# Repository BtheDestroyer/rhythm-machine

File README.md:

# rhythm-machine

Arcade style rhythm game powered by the RP2040 microprocessor.

## To Do

- The Pico's power supply isn't sufficient for running the amp + speaker. A new one will have to be added to the PCB.
- The audio amp and SD card reader modules should be worked into the PCB directly rather than third-party items.
- Potentially ditch the Pico by integrating the RP2040 into the main PCB directly.

## Materials

Most links below are to Adafruit. None are affiliate links.

- 1x [Raspberry Pi Pico](https://www.adafruit.com/product/4864)
- 1x [3 inch, 3 watt speaker](https://www.adafruit.com/product/1314)
- 6x [Arcade buttons](https://www.adafruit.com/product/473)
  - Note: Get 2 of 3 different colors; Red + Green + Bluefloat
- 6x [Quick-connect JST cables](https://www.adafruit.com/product/1152)
  - Note: The link is to a pack of 10, so just one pack will be sufficient.
- 6x [2-Pin JST-XH connectors](https://www.digikey.com/en/products/detail/jst-sales-america-inc/B2B-XH-A-LF-SN/1651045)
- 1x [Micro SD card slot breakout board](https://www.adafruit.com/product/4682)
  - [Bulk alternative](https://www.amazon.com/gp/product/B0989SM146/)
- 1x [Micro SD card](https://www.amazon.com/SanDisk-COMINU024966-16GB-microSD-Card/dp/B004KSMXVM/)
  - Note: Avoid overpaying for these for projects. I'd recommend getting [a pack of 10 cards](https://www.amazon.com/dp/B0876H387X) between 8 and 32 GB.
- 1x [Class D audio amp](https://www.adafruit.com/product/2130)
- 1x [1602 LCD with 3.3v I2C adapter](https://www.amazon.com/gp/product/B08MPTND1V/)
  - Note: You can buy these pre-soldered, but you'll need to trim the pins down which may damage your wire cutters. I'd recommend getting some [cheap disposable ones](https://www.amazon.com/Hakko-CHP-170-Micro-Cutter/dp/B00FZPDG1K/) for this purpose.
- 45x [WS2812 addressable RGB LEDs](https://www.amazon.com/gp/product/B088BRY2SH/)
  - Note: Only 44 will be visible, but I'm using one as a makeshift logic level shifter.
- 1x Zener diode
  - [Various diode pack](https://www.amazon.com/EEEEE-Assortment-Rectifier-Recovery-Switching/dp/B08SBTS2KZ/)
  - This is only necessary if you're using one of the LEDs as a makeshift logic level shifter. If you have a dedicated logic level shifter, this isn't necessary
- 1x [75mm 10 kOhm Linear Slide Potentiometer](https://www.amazon.com/dp/B09NX39NWR?psc=1&ref=ppx_yo2ov_dt_b_product_details)
- 1x 47uF capacitor
  - [Electrolytic capacitor pack](https://www.amazon.com/BOJACK-Electrolytic-Capacitor-Assortment-0-1uF－1000uF/dp/B07PBQXQNQ/)
- 1x 10nF capacitor
  - [Ceramic capacitor pack](https://www.amazon.com/DYWISHKEY-Monolithic-Multilayer-Capacitors-0-1uF-100nF/dp/B07QGDGGZV/)
- 1x 100 Ohm resistor
- 1x 220 Ohm resistor
- 1x 1.8 kOhm resistor
  - [Resistor pack](https://www.amazon.com/BOJACK-Values-Resistor-Resistors-Assortment/dp/B08FD1XVL6/)
- 4x M3 6mm screws
- 4x M3 8mm screws
- 8x M3 nuts
- 2x M3 heat-set inserts
- 2x M2 8mm screws
  - For the above assembly hardware, I'd highly recommend just searching around for a kit. There are many options that offer different screw sizes, heads, bits, etc.

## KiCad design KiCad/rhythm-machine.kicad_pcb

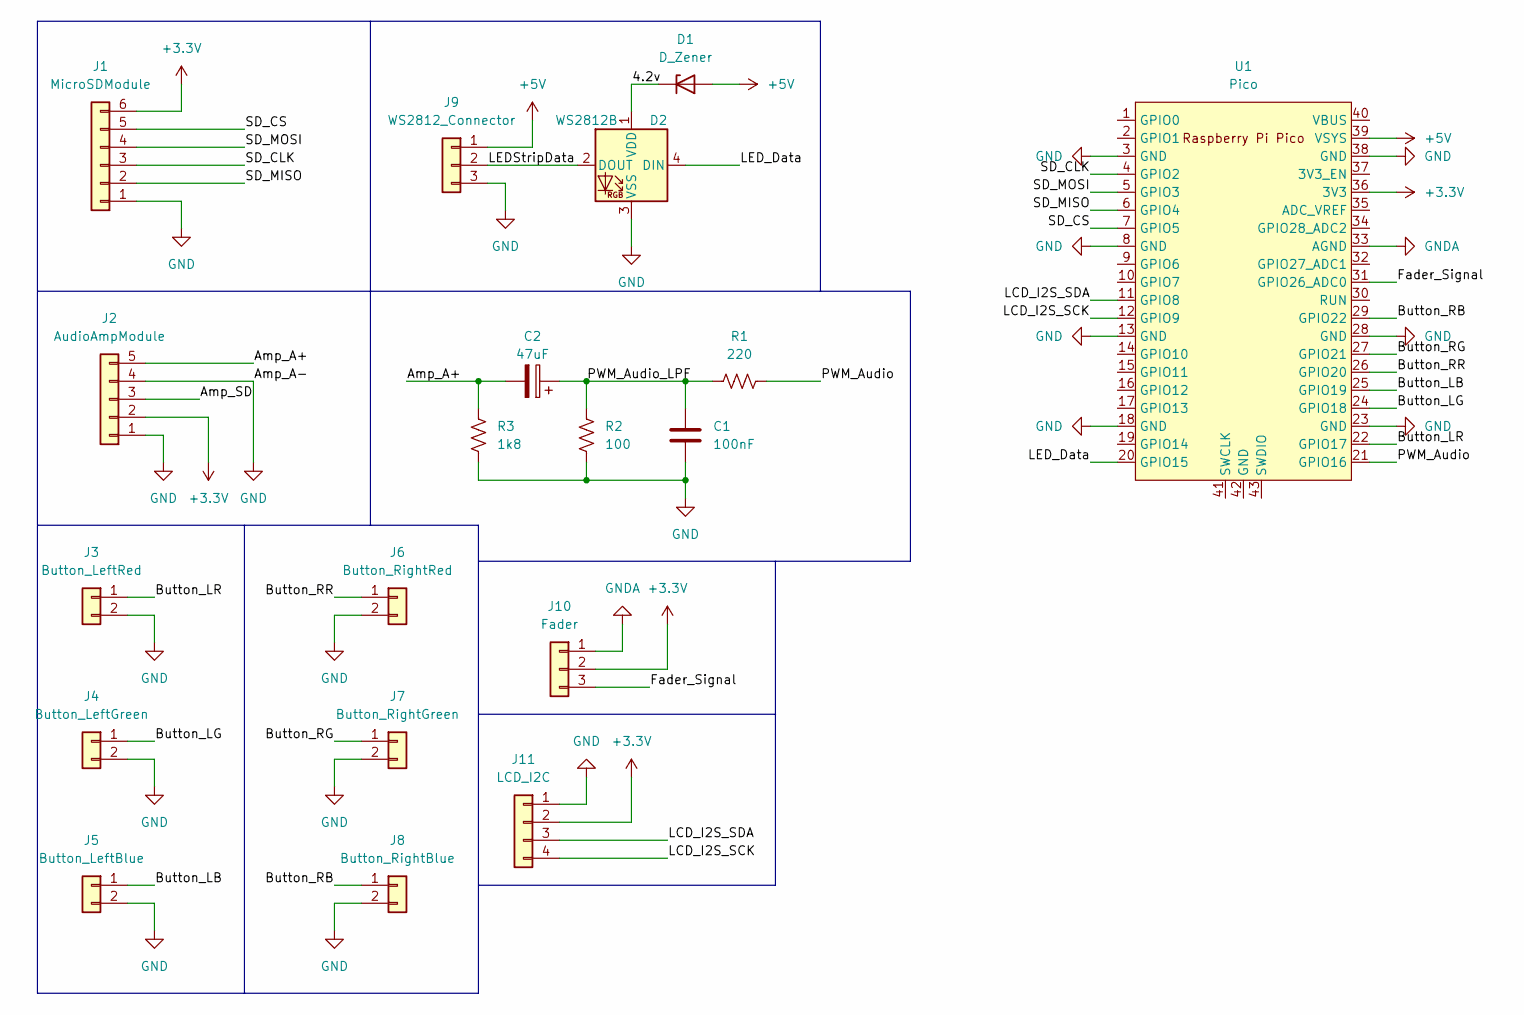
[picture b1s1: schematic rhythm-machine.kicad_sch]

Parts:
C1: 100nF; C_Disc_D4.3mm_W1.9mm_P5.00mm
C2: 47uF; CP_Radial_D4.0mm_P2.00mm
D1: D_Zener; D_T-1_P5.08mm_Horizontal
D2: WS2812B; WS2812B_Strip_Single
J1: MicroSDModule; PinHeader_1x06_P2.54mm_Vertical
J2: AudioAmpModule; PinHeader_1x05_P2.54mm_Vertical
J3: Button_LeftRed; JST_XH_B2B-XH-A_1x02_P2.50mm_Vertical
J4: Button_LeftGreen; JST_XH_B2B-XH-A_1x02_P2.50mm_Vertical
J5: Button_LeftBlue; JST_XH_B2B-XH-A_1x02_P2.50mm_Vertical
J6: Button_RightRed; JST_XH_B2B-XH-A_1x02_P2.50mm_Vertical
J7: Button_RightGreen; JST_XH_B2B-XH-A_1x02_P2.50mm_Vertical
J8: Button_RightBlue; JST_XH_B2B-XH-A_1x02_P2.50mm_Vertical
J9: WS2812_Connector; PinHeader_1x03_P2.54mm_Vertical
J10: Fader; PinHeader_1x03_P2.54mm_Vertical
J11: LCD_I2C; PinHeader_1x04_P2.54mm_Vertical
R1: 220; R_Axial_DIN0207_L6.3mm_D2.5mm_P7.62mm_Horizontal
R2: 100; R_Axial_DIN0207_L6.3mm_D2.5mm_P7.62mm_Horizontal
R3: 1k8; R_Axial_DIN0207_L6.3mm_D2.5mm_P7.62mm_Horizontal
U1: Pico; RPi_Pico_SMD_TH

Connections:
+3V3: J1.6, J2.2, J10.2, J11.2, U1.36 (3V3)
+5V: D1.2 (A), J9.1, U1.39 (VSYS)
/4.2v: D1.1 (K), D2.1 (VDD)
/Amp_A+: C2.2, J2.5, R3.2
/Amp_SD: J2.3
/Button_LB: J5.1, U1.25 (GPIO19)
/Button_LG: J4.1, U1.24 (GPIO18)
/Button_LR: J3.1, U1.22 (GPIO17)
/Button_RB: J8.1, U1.29 (GPIO22)
/Button_RG: J7.1, U1.27 (GPIO21)
/Button_RR: J6.1, U1.26 (GPIO20)
/Fader_Signal: J10.3, U1.31 (GPIO26_ADC0)
/LCD_I2S_SCK: J11.4, U1.12 (GPIO9)
/LCD_I2S_SDA: J11.3, U1.11 (GPIO8)
/LEDStripData: D2.2 (DOUT), J9.2
/LED_Data: D2.4 (DIN), U1.20 (GPIO15)
/PWM_Audio: R1.2, U1.21 (GPIO16)
/PWM_Audio_LPF: C1.2, C2.1, R1.1, R2.2
/SD_CLK: J1.3, U1.4 (GPIO2)
/SD_CS: J1.5, U1.7 (GPIO5)
/SD_MISO: J1.2, U1.6 (GPIO4)
/SD_MOSI: J1.4, U1.5 (GPIO3)
GND: C1.1, D2.3 (VSS), J1.1, J2.1, J2.4, J3.2, J4.2, J5.2, J6.2, J7.2, J8.2, J9.3, J11.1, R2.1, R3.1, U1.3 (GND), U1.8 (GND), U1.13 (GND), U1.18 (GND), U1.23 (GND), U1.28 (GND), U1.38 (GND)
GNDA: J10.1, U1.33 (AGND)

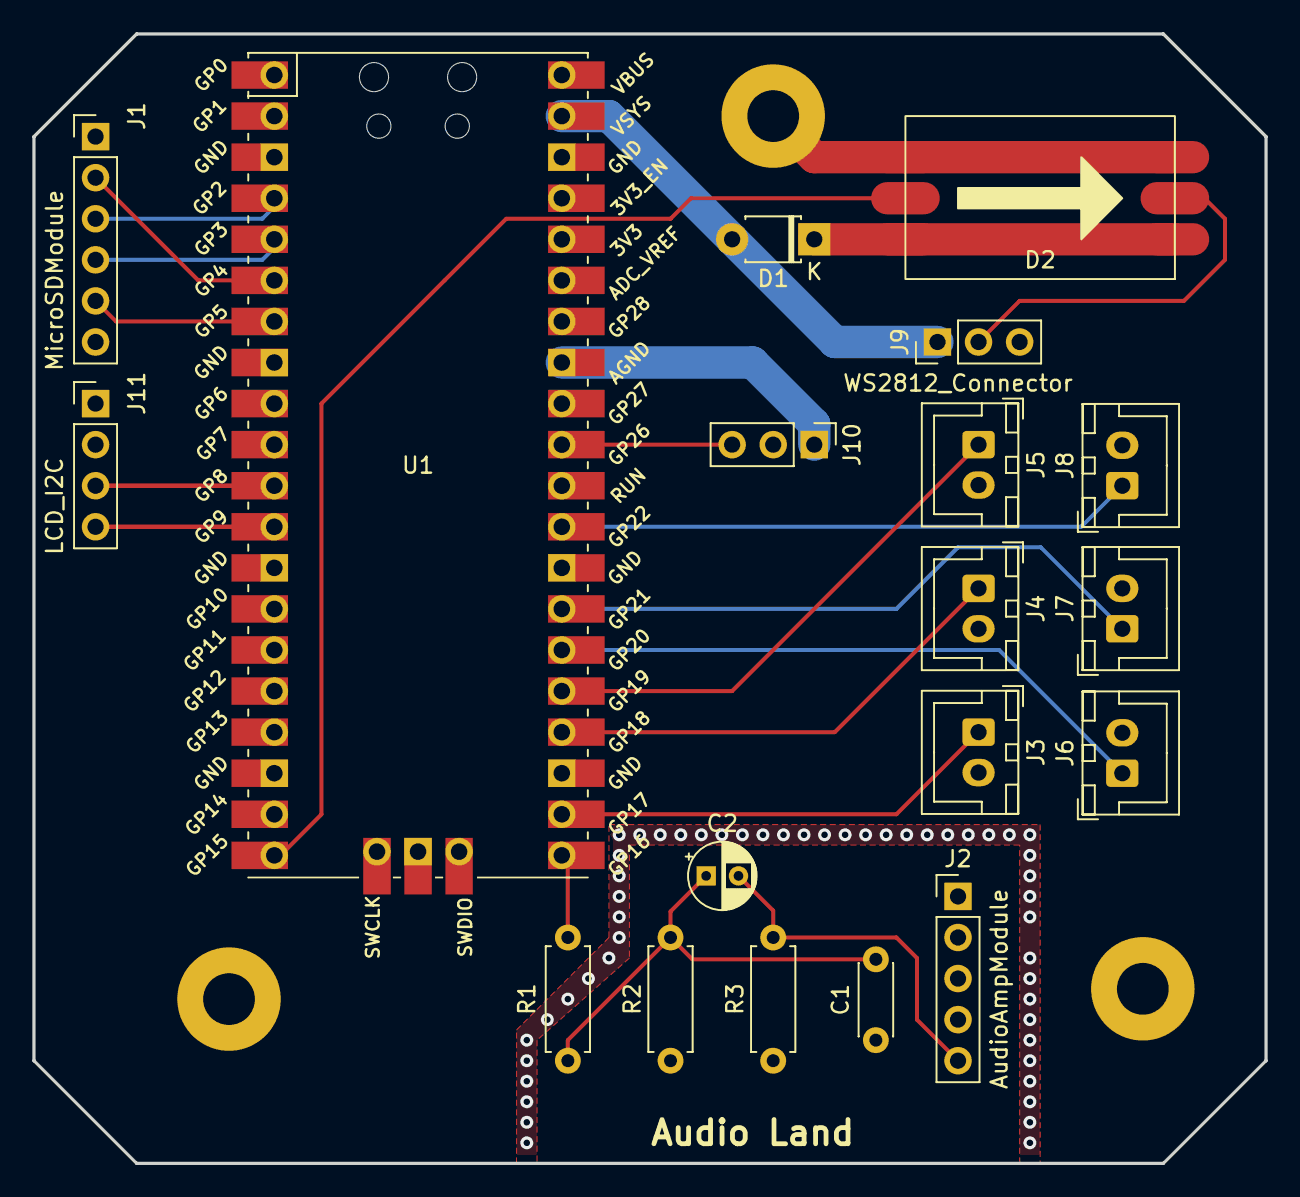
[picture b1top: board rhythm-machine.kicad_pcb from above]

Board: 4 copper layers, 76.2 x 69.8 mm, 19 parts (0 on the bottom side), 23 nets.

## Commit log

2023-05-01 First weekend of work
2023-05-01 Added model
2023-05-01 Added prototype image
2023-05-01 Added material list to README
2023-05-01 Created PCB and schematic
2023-05-01 Updated pcb for production
2023-05-01 Added image of schematic
2023-05-01 Added schematic to readme
2023-05-01 Removed autosaved files
2023-05-02 Connected Pico to GND net
2023-05-02 Split many function definitions into their own cpp files
2023-05-04 Added song data structs; started note->led rendering
2023-05-05 Added python script for converting song data yaml to binary format
2023-05-05 Added a few bytes of padding to notes to make them an even 16
2023-05-05 updated compiled binary
2023-05-05 Added .note file format data
2023-05-07 Made song_compiler.py more maintainable
2023-05-07 Song note data now loads from the SD card
